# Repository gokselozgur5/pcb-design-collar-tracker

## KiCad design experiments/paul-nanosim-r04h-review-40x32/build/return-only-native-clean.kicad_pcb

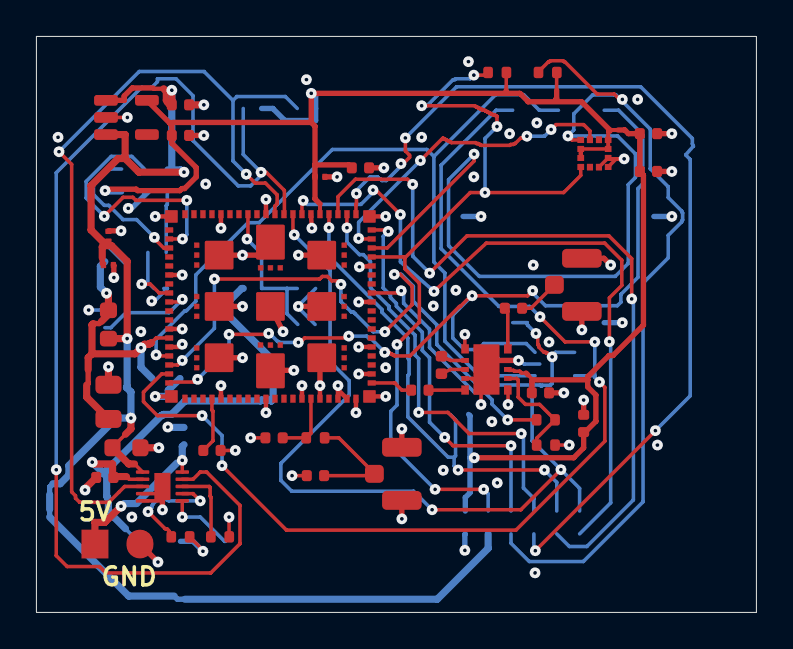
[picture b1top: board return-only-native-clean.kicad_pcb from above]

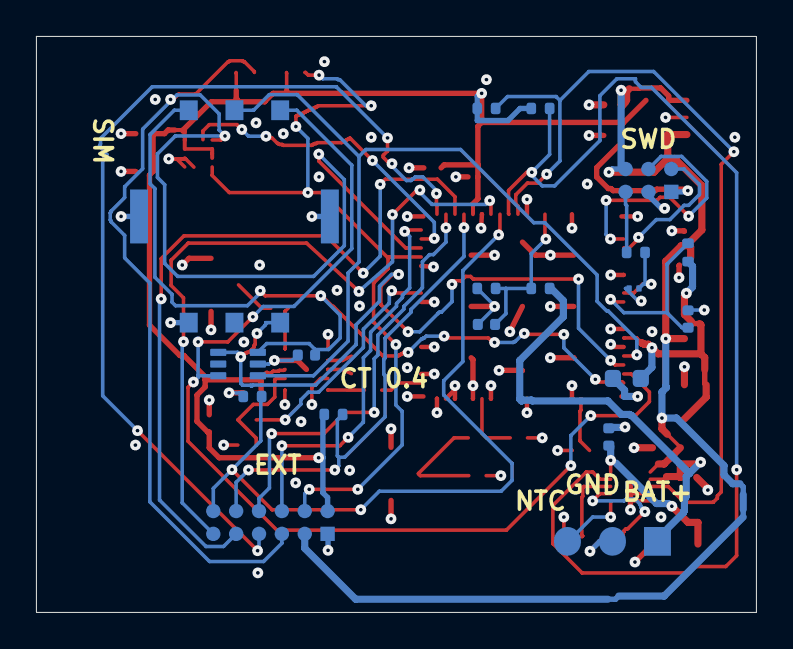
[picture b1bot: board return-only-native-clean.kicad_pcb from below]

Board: 4 copper layers, 40.0 x 32.0 mm, 54 parts (19 on the bottom side), 42 nets.

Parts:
C1: 1uF /10V; C1_C_0201_0603Metric
C2: 1uF /10V; C2_C_0201_0603Metric
C3: 47uF /10V; C3_C_0805_2012Metric
C4: 10uF /10V; C4_C_0603_1608Metric
C5: 100nF; C5_C_0201_0603Metric
C6: 4.7uF; C6_C_0402_1005Metric
C7: 4.7uF; C7_C_0402_1005Metric
C8: 100nF; C8_C_0201_0603Metric
C9: 100nF; C9_C_0402_1005Metric
C10: 100nF; C10_C_0402_1005Metric
C11: DNP / tune; C11_C_0402_1005Metric
C12: DNP / tune; C12_C_0402_1005Metric
C13: 39pF RF; C13_C_0402_1005Metric
C14: 39pF RF; C14_C_0402_1005Metric
C15: 100nF; C15_C_0402_1005Metric
C16: 1uF; C16_C_0402_1005Metric
C17: 1uF /10V; C17_C_0402_1005Metric
C18: 10uF /10V; C18_C_0603_1608Metric
C19: 1uF /10V; C19_C_0402_1005Metric
C20: 1uF; C20_C_0402_1005Metric
C21: 1uF; C21_C_0402_1005Metric
C22: 10nF; C22_C_0402_1005Metric
C23: 100nF; C23_C_0402_1005Metric
C24: 100nF; C24_C_0402_1005Metric
D1: TPD4E1U06DCKR
FB1: 22R @100MHz; FB1_L_0603_1608Metric
J1: LTE antenna / 50R; J1_U.FL_Hirose_U.FL-R-SMT-1_Vertical
J2: GNSS antenna / passive; J2_U.FL_Hirose_U.FL-R-SMT-1_Vertical
J3: 5V charging input; J3_Solder_1x02_P2.5mm
J4: Protected cell + NTC; J4_Solder_1x03_P2.5mm
J5: DIGITAL health sensor interface; J5_Contact_2x06_P1.27mm
J6: SIM8051-6-0-14-00-A; SIM8051_6_0_14_00_A
J7: SWD / debug; J7_Contact_2x03_P1.27mm
L1: 9.1nH; L1_L_0402_1005Metric
R1: 10k; R1_R_0402_1005Metric
R2: 1k; R2_R_0402_1005Metric
R3: 0R / tune; R3_R_0402_1005Metric
R4: 1k; R4_R_0402_1005Metric
R5: 100k; R5_R_0402_1005Metric
R6: 18k /1%; R6_R_0402_1005Metric
R7: 3k /1%; R7_R_0402_1005Metric
R8: 10k; R8_R_0402_1005Metric
R9: 10k; R9_R_0402_1005Metric
R10: 2M; R10_R_0402_1005Metric
R11: 1M; R11_R_0402_1005Metric
R12: 4.7k; R12_R_0402_1005Metric
R13: 4.7k; R13_R_0402_1005Metric
R14: 100k; R14_R_0402_1005Metric
R15: 100k; R15_R_0402_1005Metric
U1: nRF9151-LACA; U1_LGA_9151_12.1x11.1mm
U2: SKY65943-11; U2_SKY65943_DK10171
U3: BQ25185DLHR; U3_Texas_DLH0010A_WSON-10-1EP_2.2x2mm_P0.4mm_EP0.9x1.5mm
U4: TPS7A0218PDBVR; U4_SOT-23-5
U5: LIS2DW12TR; U5_LGA-12_2x2mm_P0.5mm

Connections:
/ACC_INT: U1.58, U5.12
/AMP_IN: L1.2, U2.8
/BAT_ADC: C22.1, R10.2, R11.1, U1.73
/BAT_NTC: J4.3, U3.6
/CHG_FAULT: R9.1, U1.70, U3.3
/CHG_STAT: R8.1, U1.69, U3.9
/COEX0: R4.1, U1.52
/DEBUG_RESET: J7.5, R2.2
/DEC0: C7.1, U1.24
/FILT_OUT: L1.1, U2.7
/GND: C1.2, C2.2, C3.2, C4.2, C5.2, C6.2, C7.2, C8.2, C9.2, C10.2, C11.2, C12.2, C15.2, C16.2, C17.2, C18.2, C19.2, C20.2, C21.2, C22.2, C23.2, C24.2, D1.2, J1.2, J2.2, J3.2, J4.2, J5.1, J6.5, J6.8, J7.3, R5.2, R6.2, R7.2, R11.2, R15.2, U1.1, U1.7, U1.13, U1.15, U1.20, U1.25, U1.30, U1.34, U1.36, U1.38, U1.39, U1.40, U1.41, U1.43, U1.46, U1.51, U1.55, U1.60, U1.66, U1.71, U1.76, U1.105, U1.106, U1.107, U1.108, U1.109, U1.110, U1.111, U1.112, U1.113, U2.1, U2.4, U2.6, U2.9, U2.11, U3.4, U3.5, U3.11, U4.2, U5.6, U5.7, U5.8
/GNSS_ANT: C14.1, J2.1
/GNSS_FEM_IN: C14.2, U2.5
/GNSS_FEM_OUT: C13.1, U2.10
/GNSS_LNA_EN: R4.2, R5.1, U2.2
/GPS_RF: C13.2, U1.42
/HEALTH_CS: J5.10, R14.1, U1.64
/HEALTH_EN: J5.12, R15.1, U1.68
/HEALTH_INT: J5.6, U1.59
/HEALTH_RESET: J5.11, U1.67
/I2C_SCL: J5.5, R13.1, U1.57, U5.1
/I2C_SDA: J5.4, R12.1, U1.56, U5.4
/ILIM_VSET: R6.1, U3.7
/ISET: R7.1, U3.8
/LTE_ANT: C12.1, J1.1, R3.2
/LTE_RF: C11.1, R3.1, U1.35
/NRF_ENABLE: C9.1, R1.2, U1.10
/NRF_RESET: C8.1, R2.1, U1.9
/SIM_1V8: C10.1, D1.3, J6.1, U1.19
/SIM_CLK: D1.6, J6.3, U1.18
/SIM_IO: D1.4, J6.7, U1.17
/SIM_RST: D1.1, J6.2, U1.16
/SPI_MISO: J5.9, U1.63
/SPI_MOSI: J5.8, U1.62
/SPI_SCK: J5.7, U1.61
/SWDCLK: J7.4, U1.3
/SWDIO: J7.2, U1.4
/VBAT: C19.1, J4.1, R10.1, U3.2
/VDD_NRF: C3.1, C4.1, FB1.2, R1.1, U1.14
/VIN_5V: C17.1, J3.1, U3.10
/VIO_1V8: C5.1, C6.1, C15.1, C16.1, C21.1, C23.1, C24.1, J5.2, J7.1, R8.2, R9.2, R12.2, R13.2, R14.2, U1.65, U2.3, U4.5, U5.2, U5.3, U5.9, U5.10
/VSYS: C1.1, C2.1, C18.1, C20.1, FB1.1, J5.3, J7.6, U3.1, U4.1, U4.3

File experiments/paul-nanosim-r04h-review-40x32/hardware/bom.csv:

ref,value,mpn,footprint,dnp,onboard,status,lcsc
U1,nRF9151-LACA,NRF9151-LACA-R,Collar033:U1_LGA_9151_12.1x11.1mm,False,True,candidate; LTE-M carrier unresolved,
FB1,22R @100MHz,BLM18SD220SN1,Collar033:FB1_L_0603_1608Metric,False,True,Nordic recommended filter; verify rail impedance,
C1,1uF /10V,GRM033R61A105ME15,Collar033:C1_C_0201_0603Metric,False,True,candidate,
C2,1uF /10V,GRM033R61A105ME15,Collar033:C2_C_0201_0603Metric,False,True,candidate,
C3,47uF /10V,GRM21BR61A476ME15,Collar033:C3_C_0805_2012Metric,False,True,candidate,
C4,10uF /10V,GRM188R61A106MAAL,Collar033:C4_C_0603_1608Metric,False,True,candidate,
C5,100nF,GRM033R60J104ME19,Collar033:C5_C_0201_0603Metric,False,True,candidate,
C6,4.7uF,GRM155R60J475ME47,Collar033:C6_C_0402_1005Metric,False,True,candidate,
C7,4.7uF,GRM155R60J475ME47,Collar033:C7_C_0402_1005Metric,False,True,candidate,
C8,100nF,,Collar033:C8_C_0201_0603Metric,False,True,candidate,
R1,10k,,Collar033:R1_R_0402_1005Metric,False,True,candidate,
C9,100nF,,Collar033:C9_C_0402_1005Metric,False,True,candidate,
R2,1k,,Collar033:R2_R_0402_1005Metric,False,True,candidate,
C10,100nF,,Collar033:C10_C_0402_1005Metric,False,True,SIM supply decoupling beside the upper contact row,
R3,0R / tune,,Collar033:R3_R_0402_1005Metric,False,True,candidate,
C11,DNP / tune,,Collar033:C11_C_0402_1005Metric,True,True,candidate,
C12,DNP / tune,,Collar033:C12_C_0402_1005Metric,True,True,candidate,
J1,LTE antenna / 50R,U.FL-R-SMT-1(10),Collar033:J1_U.FL_Hirose_U.FL-R-SMT-1_Vertical,False,True,bench connector; final FPC antenna TBD,
U2,SKY65943-11,SKY65943-11,Collar033:U2_SKY65943_DK10171,False,True,DFM layout candidate; electrical validation pending,
L1,9.1nH,LQW15AN9N1J00D,Collar033:L1_L_0402_1005Metric,False,True,candidate,
C13,39pF RF,,Collar033:C13_C_0402_1005Metric,False,True,candidate,
C14,39pF RF,,Collar033:C14_C_0402_1005Metric,False,True,candidate,
J2,GNSS antenna / passive,U.FL-R-SMT-1(10),Collar033:J2_U.FL_Hirose_U.FL-R-SMT-1_Vertical,False,True,bench connector; final antenna/ESD TBD,
R4,1k,,Collar033:R4_R_0402_1005Metric,False,True,candidate,
R5,100k,,Collar033:R5_R_0402_1005Metric,False,True,candidate,
C15,100nF,,Collar033:C15_C_0402_1005Metric,False,True,candidate,
C16,1uF,,Collar033:C16_C_0402_1005Metric,False,True,candidate,
J3,5V charging input,,Collar033:J3_Solder_1x02_P2.5mm,False,True,onboard contact pads; external device/fixture not selected,
U3,BQ25185DLHR,BQ25185DLHR,Collar033:U3_Texas_DLH0010A_WSON-10-1EP_2.2x2mm_P0.4mm_EP0.9x1.5mm,False,True,DFM layout candidate; electrical validation pending,
J4,Protected cell + NTC,,Collar033:J4_Solder_1x03_P2.5mm,False,True,onboard contact pads; external device/fixture not selected,
C17,1uF /10V,,Collar033:C17_C_0402_1005Metric,False,True,candidate,
C18,10uF /10V,,Collar033:C18_C_0603_1608Metric,False,True,candidate,
C19,1uF /10V,,Collar033:C19_C_0402_1005Metric,False,True,candidate,
R6,18k /1%,,Collar033:R6_R_0402_1005Metric,False,True,4.2V / 500mA input limit per BQ25185 table,
R7,3k /1%,,Collar033:R7_R_0402_1005Metric,False,True,100mA provisional; battery approval required,
R8,10k,,Collar033:R8_R_0402_1005Metric,False,True,candidate,
R9,10k,,Collar033:R9_R_0402_1005Metric,False,True,candidate,
U4,TPS7A0218PDBVR,TPS7A0218PDBVR,Collar033:U4_SOT-23-5,False,True,candidate; VIO sequencing unresolved,
C20,1uF,,Collar033:C20_C_0402_1005Metric,False,True,candidate,
C21,1uF,,Collar033:C21_C_0402_1005Metric,False,True,candidate,
R10,2M,,Collar033:R10_R_0402_1005Metric,False,True,candidate,
R11,1M,,Collar033:R11_R_0402_1005Metric,False,True,candidate,
C22,10nF,,Collar033:C22_C_0402_1005Metric,False,True,candidate,
U5,LIS2DW12TR,LIS2DW12TR,Collar033:U5_LGA-12_2x2mm_P0.5mm,False,True,DFM layout candidate; electrical validation pending,
C23,100nF,,Collar033:C23_C_0402_1005Metric,False,True,candidate,
C24,100nF,,Collar033:C24_C_0402_1005Metric,False,True,candidate,
R12,4.7k,,Collar033:R12_R_0402_1005Metric,False,True,candidate,
R13,4.7k,,Collar033:R13_R_0402_1005Metric,False,True,candidate,
J5,DIGITAL health sensor interface,,Collar033:J5_Contact_2x06_P1.27mm,False,True,onboard contact pads; external device/fixture not selected,
R14,100k,,Collar033:R14_R_0402_1005Metric,False,True,candidate,
R15,100k,,Collar033:R15_R_0402_1005Metric,False,True,candidate,
J6,SIM8051-6-0-14-00-A,SIM8051-6-0-14-00-A,Collar04:SIM8051_6_0_14_00_A,False,True,SMT removable nano-SIM; 1.8V UICC and LTE-M/NB-IoT service required,C7363812
J7,SWD / debug,,Collar033:J7_Contact_2x03_P1.27mm,False,True,onboard contact pads; external device/fixture not selected,
D1,TPD4E1U06DCKR,TPD4E1U06DCKR,Collar04:TPD4E1U06DCKR,False,True,Three upper SIM contacts; short connector-side ESD routes,C194628
D2,TPD4E1U06DCKR,TPD4E1U06DCKR,Collar04:TPD4E1U06DCKR,False,True,Lower SIM data contact; direct connector-to-ESD-to-modem route,C194628
